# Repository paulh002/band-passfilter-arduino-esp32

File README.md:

# band-passfilter-arduino-esp32
ESP32 managed HF bandpass filter
The PCB supports 4 7 order bandpass filters. The filters are switched using AS169 gasfet switches.
The filters can be designed using elsie software of tonnesoftware (until 7th order free)  http://tonnesoftware.com/elsie.html
The AS169 are switched by using I2C 2x PCF8574A. The boards can be cascaded.

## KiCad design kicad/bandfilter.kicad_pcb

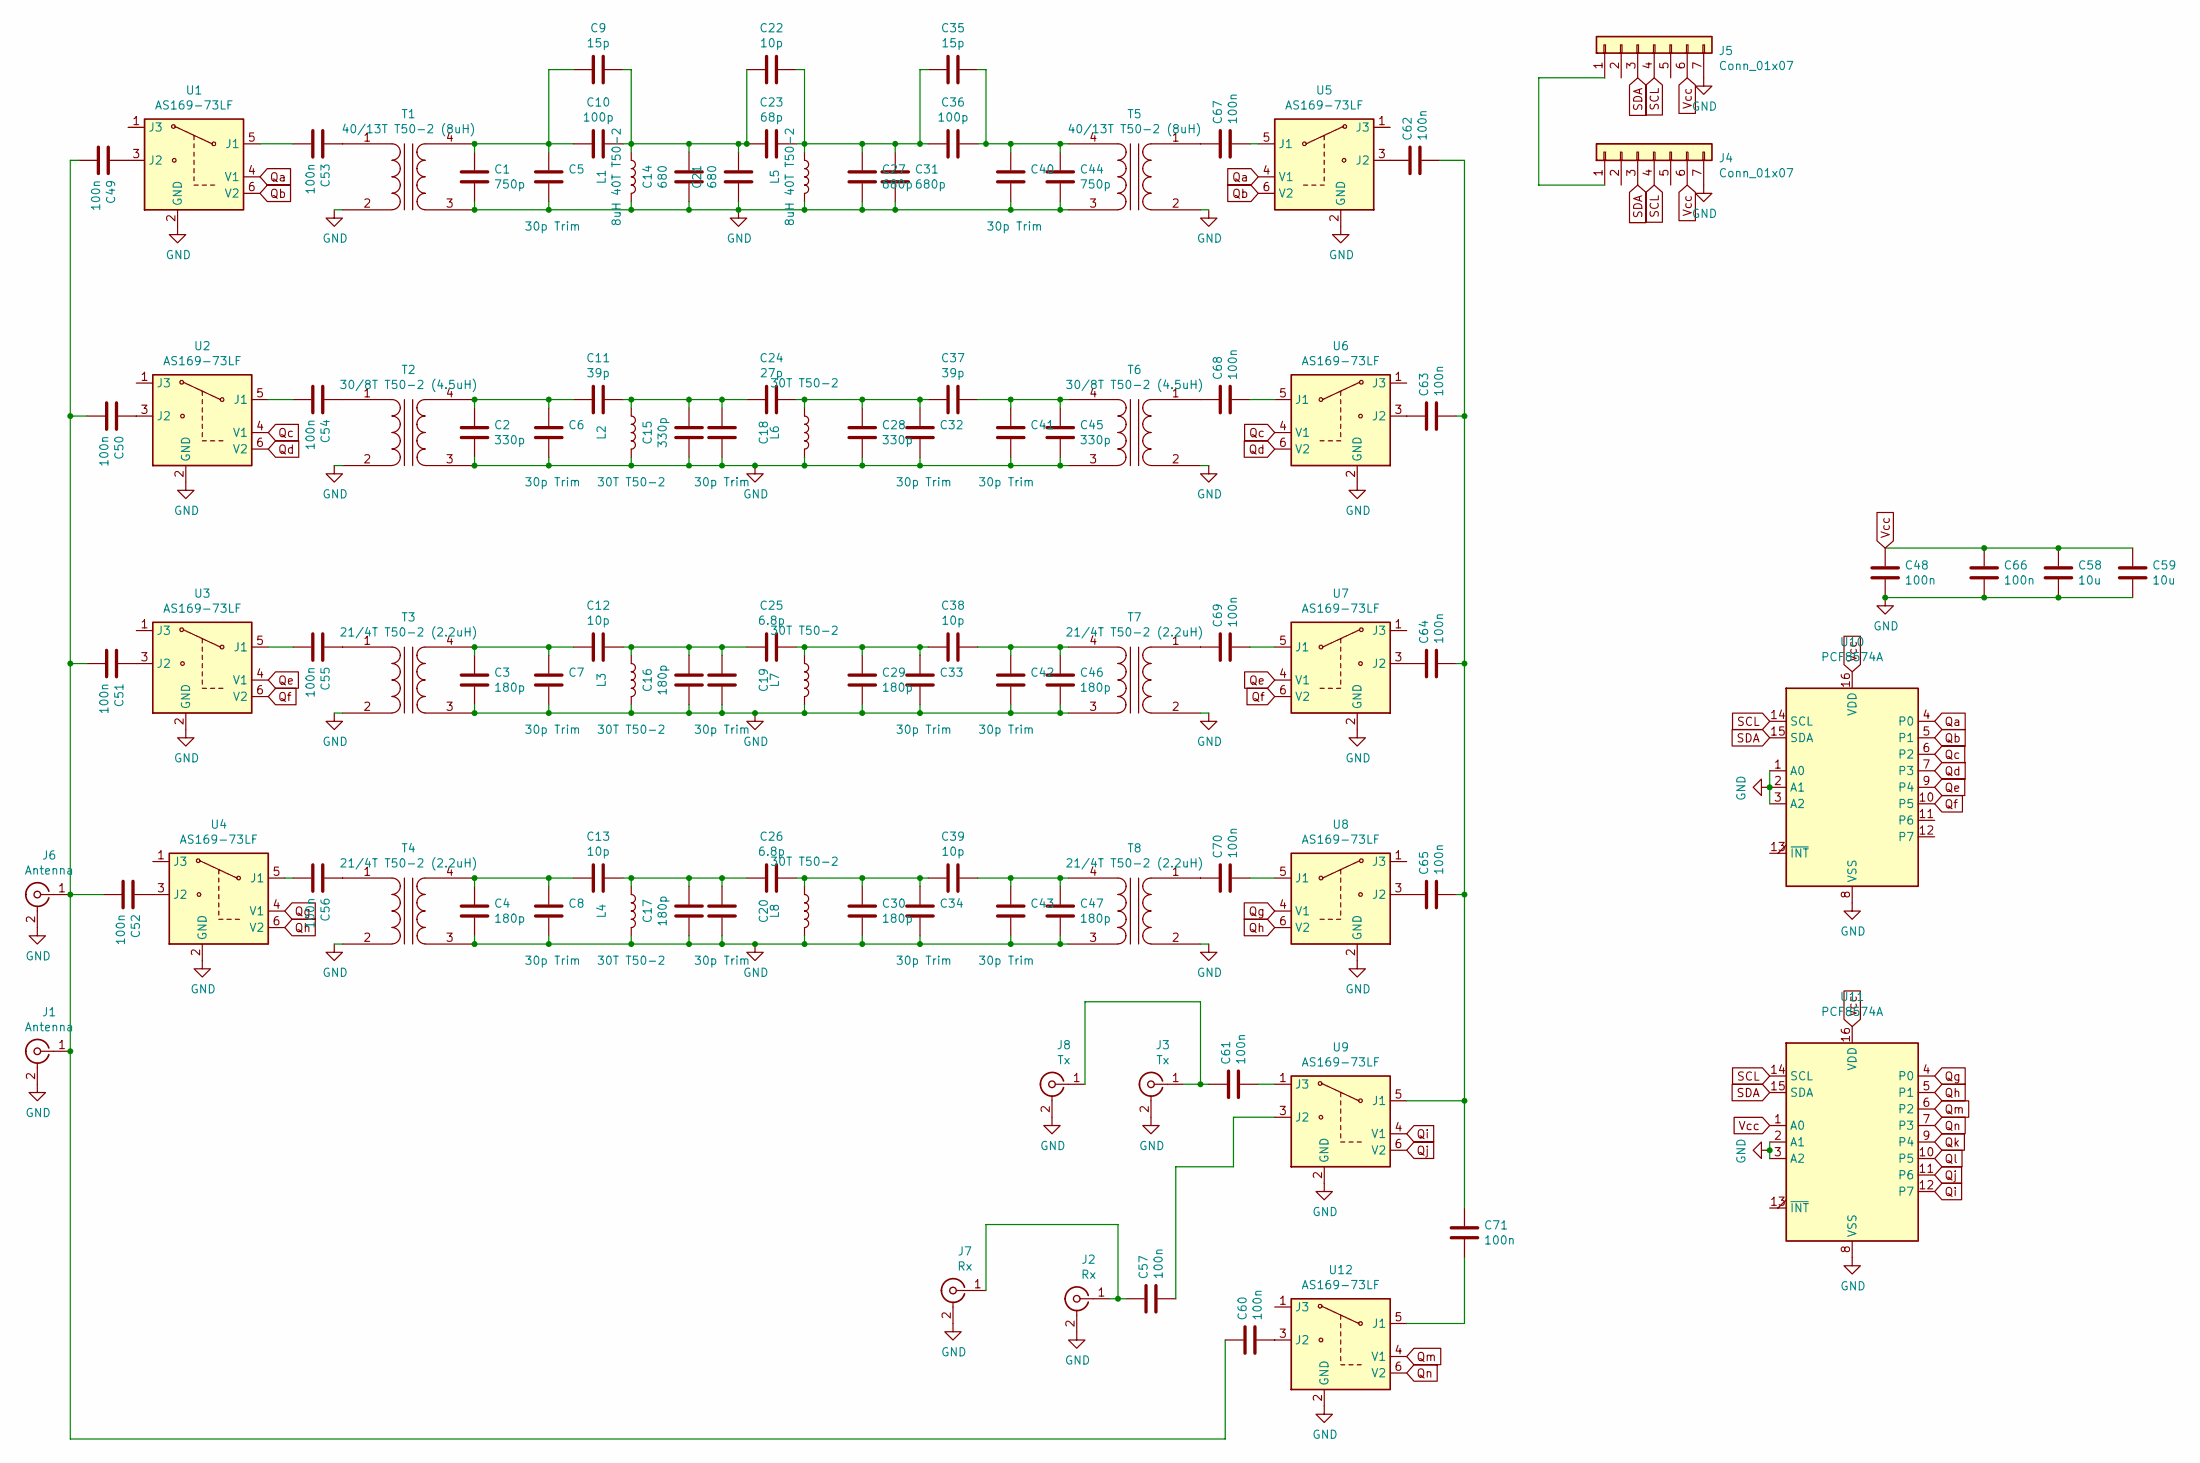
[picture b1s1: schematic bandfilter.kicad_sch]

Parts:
C1: 750p; C_0805_2012Metric_Pad1.15x1.40mm_HandSolder
C2, C15, C28: 330p; C_0805_2012Metric_Pad1.15x1.40mm_HandSolder
C3, C4, C16, C17, C29, C30: 180p; C_0805_2012Metric_Pad1.15x1.40mm_HandSolder
C5, C6, C7, C8, C18, C19, C20, C32, C33, C34: 30p Trim; C_0805_2012Metric_Pad1.15x1.40mm_HandSolder
C9, C35: 15p; C_Disc_D9.0mm_W5.0mm_P5.00mm
C10, C36: 100p; C_0805_2012Metric_Pad1.15x1.40mm_HandSolder
C11, C37: 39p; C_Disc_D9.0mm_W5.0mm_P5.00mm
C12, C13, C22, C38, C39: 10p; C_Disc_D9.0mm_W5.0mm_P5.00mm
C14, C21: 680; C_0805_2012Metric_Pad1.15x1.40mm_HandSolder
C23: 68p; C_0805_2012Metric_Pad1.15x1.40mm_HandSolder
C24: 27p; C_Disc_D9.0mm_W5.0mm_P5.00mm
C25, C26: 6.8p; C_Disc_D9.0mm_W5.0mm_P5.00mm
C27, C31: 680p; C_0805_2012Metric_Pad1.15x1.40mm_HandSolder
C40, C41, C42, C43: 30p Trim; C_0805_2012Metric
C44: 750p; C_0805_2012Metric
C45: 330p; C_0805_2012Metric
C46, C47: 180p; C_0805_2012Metric
C48, C49, C50, C51, C52, C53, C54, C55, C56, C57, C60, C61, C62, C63, C64, C65, C66, C67, C68, C69, C70, C71: 100n; C_1206_3216Metric_Pad1.42x1.75mm_HandSolder
C58, C59: 10u; C_1206_3216Metric_Pad1.42x1.75mm_HandSolder
J1: Antenna; SMA_Amphenol_132134_Vertical
J2: Rx; SMA_Amphenol_132134_Vertical
J3: Tx; SMA_Amphenol_132134_Vertical
J4, J5: Conn_01x07; PinSocket_1x07_P2.54mm_Vertical
J6: Antenna; SMA_Amphenol_132289_EdgeMount
J7: Rx; SMA_Amphenol_132289_EdgeMount
J8: Tx; SMA_Amphenol_132289_EdgeMount
L1, L5: 8uH 40T T50-2; Transformer_Toroid_Horizontal_D14.0mm_Amidon-T50
L2, L3, L4, L6, L7, L8: 30T T50-2; Transformer_Toroid_Horizontal_D14.0mm_Amidon-T50
T1, T5: 40/13T T50-2 (8uH); Transformer_Toroid_Horizontal_D14.0mm_Amidon-T50
T2, T6: 30/8T T50-2 (4.5uH); Transformer_Toroid_Horizontal_D14.0mm_Amidon-T50
T3, T4, T7, T8: 21/4T T50-2 (2.2uH); Transformer_Toroid_Horizontal_D14.0mm_Amidon-T50
U1, U2, U3, U4, U5, U6, U7, U8, U9, U12: AS169-73LF; SOT-23-6_Handsoldering
U10, U11: PCF8574A; SOP-16_7.5x10.4mm_P1.27mm

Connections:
unnamed: C1.2, C5.2, C9.2, C10.2, T1.4 (SB)
unnamed: C9.1, C10.1, C14.1, C21.1, C22.2, C23.2, L1.1
unnamed: C11.1, C15.1, C18.2, C24.2, L2.1
unnamed: C2.2, C6.2, C11.2, T2.4 (SB)
unnamed: C12.1, C16.1, C19.2, C25.2, L3.1
unnamed: C3.2, C7.2, C12.2, T3.4 (SB)
unnamed: C13.1, C17.1, C20.2, C26.2, L4.1
unnamed: C4.2, C8.2, C13.2, T4.4 (SB)
unnamed: C22.1, C23.1, C27.2, C31.2, C35.2, C36.2, L5.1
unnamed: C24.1, C28.2, C32.2, C37.2, L6.1
unnamed: C25.1, C29.2, C33.2, C38.2, L7.1
unnamed: C26.1, C30.2, C34.2, C39.2, L8.1
unnamed: C35.1, C36.1, C40.2, C44.2, T5.4 (SB)
unnamed: C37.1, C41.2, C45.2, T6.4 (SB)
unnamed: C38.1, C42.2, C46.2, T7.4 (SB)
unnamed: C39.1, C43.2, C47.2, T8.4 (SB)
unnamed: C49.1, C50.1, C51.1, C52.1, C60.2, J1.1 (In), J6.1 (In)
unnamed: C49.2, U1.3 (J2)
unnamed: C50.2, U2.3 (J2)
unnamed: C51.2, U3.3 (J2)
unnamed: C52.2, U4.3 (J2)
unnamed: C53.1, U1.5 (J1)
unnamed: C53.2, T1.1 (AA)
unnamed: C54.1, U2.5 (J1)
unnamed: C54.2, T2.1 (AA)
unnamed: C55.1, U3.5 (J1)
unnamed: C55.2, T3.1 (AA)
unnamed: C56.1, U4.5 (J1)
unnamed: C56.2, T4.1 (AA)
unnamed: C57.1, U9.3 (J2)
unnamed: C57.2, J2.1 (In), J7.1 (In)
unnamed: C60.1, U12.3 (J2)
unnamed: C61.1, U9.1 (J3)
unnamed: C61.2, J3.1 (In), J8.1 (In)
unnamed: C62.1, C63.1, C64.1, C65.1, C71.2, U9.5 (J1)
unnamed: C62.2, U5.3 (J2)
unnamed: C63.2, U6.3 (J2)
unnamed: C64.2, U7.3 (J2)
unnamed: C65.2, U8.3 (J2)
unnamed: C67.1, U5.5 (J1)
unnamed: C67.2, T5.1 (AA)
unnamed: C68.1, U6.5 (J1)
unnamed: C68.2, T6.1 (AA)
unnamed: C69.1, U7.5 (J1)
unnamed: C69.2, T7.1 (AA)
unnamed: C70.1, U8.5 (J1)
unnamed: C70.2, T8.1 (AA)
unnamed: C71.1, U12.5 (J1)
unnamed: J4.1, J5.1
Qa: U1.4 (V1), U5.4 (V1), U10.4 (P0)
Qb: U1.6 (V2), U5.6 (V2), U10.5 (P1)
Qc: U2.4 (V1), U6.4 (V1), U10.6 (P2)
Qd: U2.6 (V2), U6.6 (V2), U10.7 (P3)
Qe: U3.4 (V1), U7.4 (V1), U10.9 (P4)
Qf: U3.6 (V2), U7.6 (V2), U10.10 (P5)
Qg: U4.4 (V1), U8.4 (V1), U11.4 (P0)
Qh: U4.6 (V2), U8.6 (V2), U11.5 (P1)
Qi: U9.4 (V1), U11.12 (P7)
Qj: U9.6 (V2), U11.11 (P6)
Qk: U11.9 (P4)
Ql: U11.10 (P5)
Qm: U11.6 (P2), U12.4 (V1)
Qn: U11.7 (P3), U12.6 (V2)
SCL: J4.4, J5.4, U10.14 (SCL), U11.14 (SCL)
SDA: J4.3, J5.3, U10.15 (SDA), U11.15 (SDA)
Vcc: C48.2, C58.2, C59.2, C66.2, J4.6, J5.6, U10.16 (VDD), U11.1 (A0), U11.16 (VDD)

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
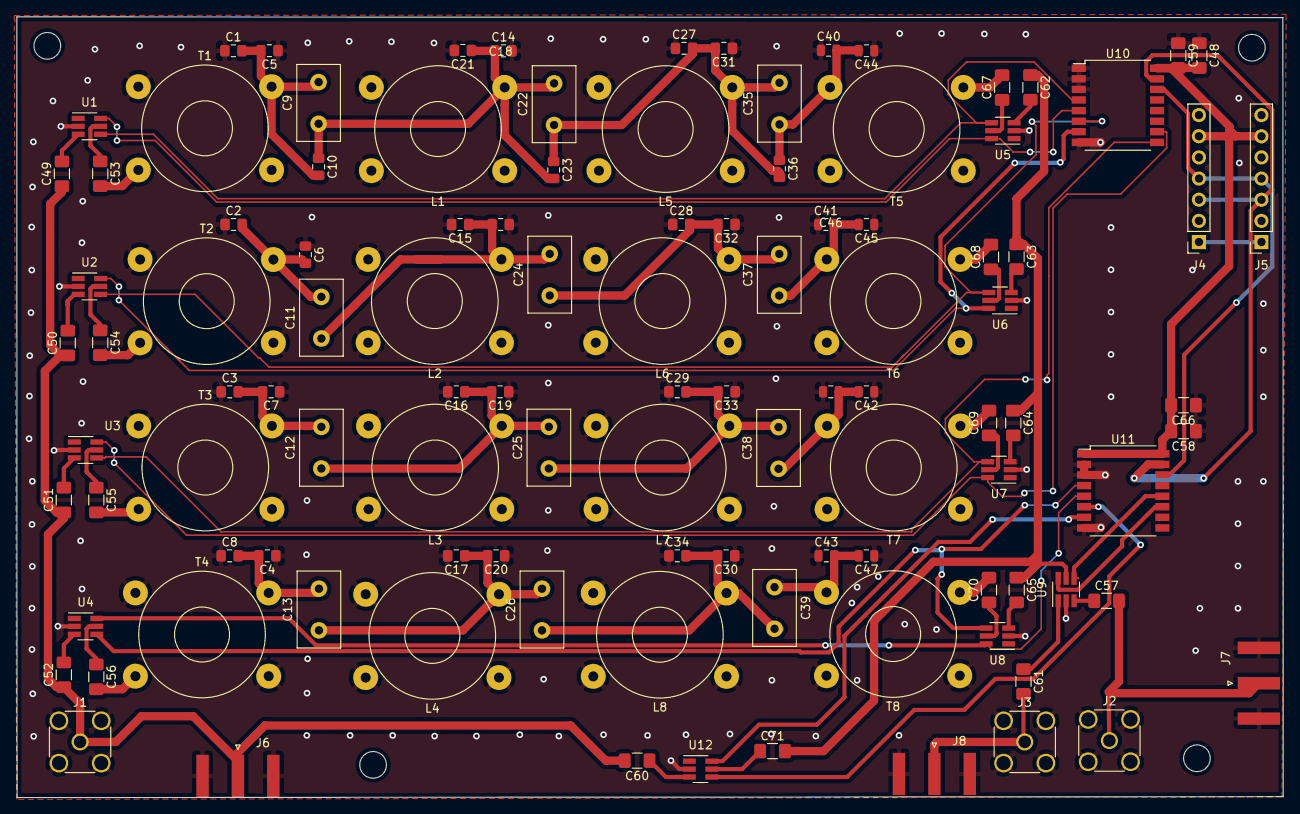
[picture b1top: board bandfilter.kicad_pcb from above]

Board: 2 copper layers, 152.0 x 93.7 mm, 111 parts (0 on the bottom side), 65 nets.

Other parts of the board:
 : MountingHole_3.2mm_M3
 #2,  #3,  #4: MountingHole_3.2mm_M3

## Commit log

2022-03-11 I2C version update
